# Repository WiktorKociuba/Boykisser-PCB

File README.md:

# Boykisser-PCB

A simple PCB, in shape of a boykisser, with 2 LEDs and a photoresistor that controls the circuit.

### Schematic

### PCB

### BOM

- 1x CR2032 battery cell
- 2x 2mm LED
- 1x 2N3904 transistor
- 1x 47k resistor
- 4x 220 resistor
- 1x GL5528 photoresistor
- 1x SPST THT switch

Made by **@Mejpek** on slack for [Solder YSWS](https://solder.hackclub.com/).

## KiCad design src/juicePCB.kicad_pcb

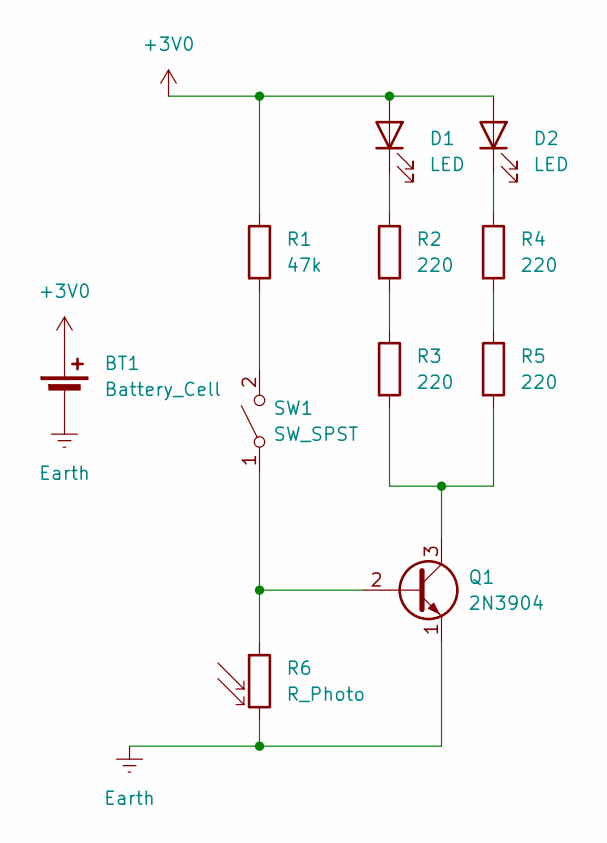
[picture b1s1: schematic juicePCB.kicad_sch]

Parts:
BT1: Battery_Cell; BatteryHolder_Keystone_3034_1x20mm
D1, D2: LED; LED_D5.0mm
Q1: 2N3904; TO-92_Inline
R1: 47k; R_Axial_DIN0207_L6.3mm_D2.5mm_P7.62mm_Horizontal
R2, R3, R4, R5: 220; R_Axial_DIN0207_L6.3mm_D2.5mm_P7.62mm_Horizontal
R6: R_Photo; R_LDR_5.1x4.3mm_P3.4mm_Vertical
SW1: SW_SPST; SW_DIP_SPSTx01_Slide_9.78x4.72mm_W7.62mm_P2.54mm

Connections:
+3V0: BT1.1 (+), D1.2 (A), D2.2 (A), R1.1
Earth: BT1.2 (-), Q1.1 (E), R6.2
unnamed: D1.1 (K), R2.1
unnamed: D2.1 (K), R4.1
unnamed: Q1.2 (B), R6.1, SW1.1 (A)
unnamed: Q1.3 (C), R3.2, R5.2
unnamed: R2.2, R3.1
unnamed: R4.2, R5.1
unnamed: R1.2, SW1.2 (B)

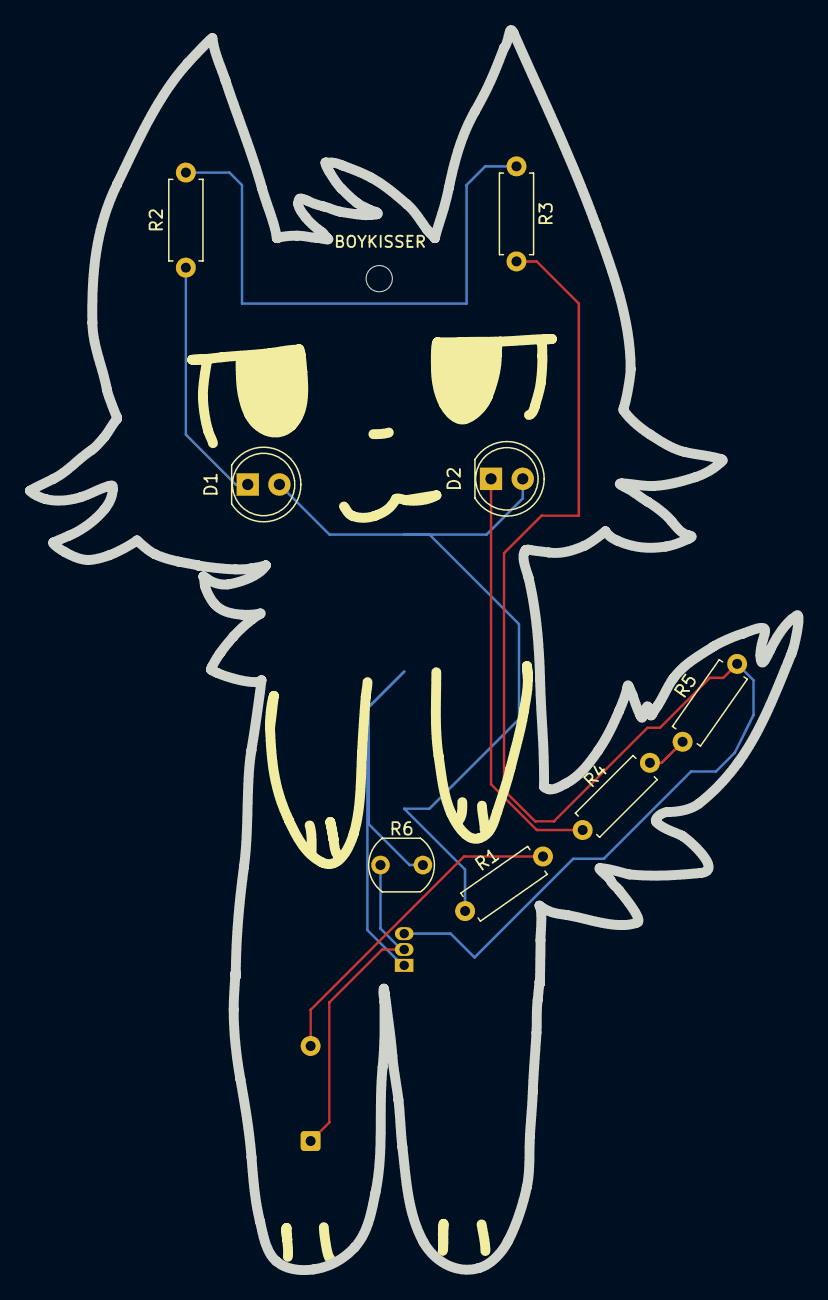
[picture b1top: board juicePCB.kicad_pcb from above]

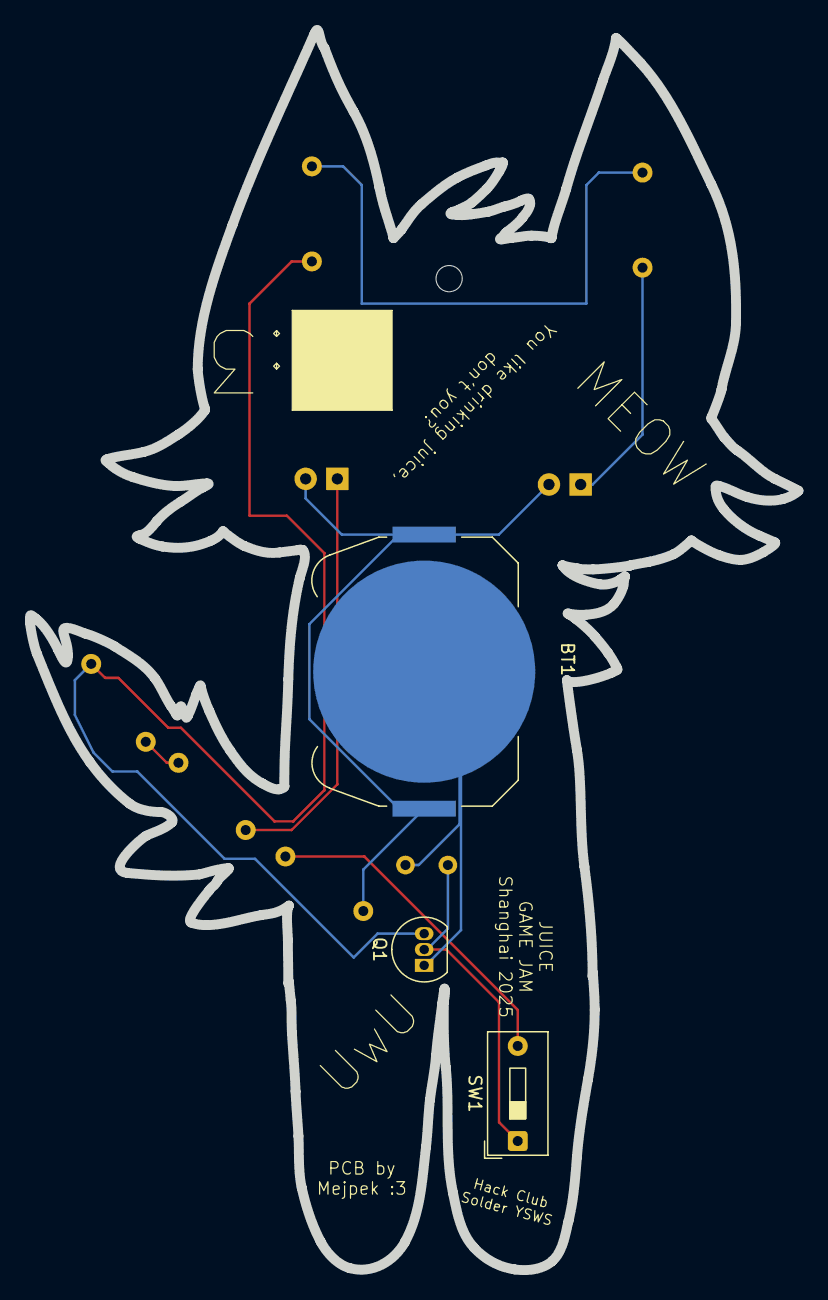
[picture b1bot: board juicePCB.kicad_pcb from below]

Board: 2 copper layers, 61.6 x 99.4 mm, 12 parts (3 on the bottom side), 9 nets.

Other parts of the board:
BOYKISSER: MountingHole_2.1mm

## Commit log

2025-04-09 Upload of the PCB design
2025-04-09 Added pictures of the pcb
2025-04-14 Zipped the gerber files
2025-05-28 Final rev.
